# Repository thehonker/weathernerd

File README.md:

# WeatherNerd

Low-power, long-duration weather stations built around the [WindNerd Core](https://github.com/windnerd-labs/Windnerd-Core) anemometer and ESP32-C6 dataloggers.

## What is this?

Two station variants sharing the same wind sensor and datalogger platform:

### Remote Station (v1)

A battery-powered, 6-month-unattended weather station for remote deployment. No grid power, no WiFi infrastructure, no maintenance visits. Deploy in fall, retrieve in spring.

- **Wind:** WindNerd Core (STM32G031F8) with custom firmware — STOP mode sleep (~5 µA), woken on demand by ESP32-C6 every 5s via GPIO interrupt. Wind speed via rotor pulse counting, direction via TMAG5273 magnetic angle sensor.
- **Datalogger:** ESP32-C6 SuperMini, running **ESP-IDF v6.1** (not Arduino — the LP RISC-V coprocessor requires ESP-IDF's `ulp_embed_binary` build system). LP core handles the 5s wind sampling loop while the main core sleeps (~7 µA deep sleep). Main core wakes every 1 min for temp/RH/pressure, rain ADC, and SD card flush.
- **Sensors:** BME280 (temp/RH/pressure, I2C), DS3231 RTC (±2 ppm, I2C), DIY piezo disdrometer (ADC, rain rate).
- **Storage:** 8 GB industrial microSD via SPI. Two daily CSV files: `YYYY-MM-DD-wind.csv` (5s samples) and `YYYY-MM-DD-env.csv` (1 min samples). ~168 MB for 6 months.
- **Power:** 2× ER34615 Li-SOCl2 D-cells (38 Ah, -55°C rated). Total system draw ~0.55 mA (16× battery headroom over 6 months). Battery lasts years — power is a non-issue.
- **Uplink:** SIM7080G Cat-M1 modem on AT&T LTE-M network. MQTT uplink every 30 min with buffered data. Daily GPS fix via SIM7080G GNSS syncs the DS3231 RTC, eliminating long-term drift. PSM sleep (~3 µA module) between uploads.
- **Retrieval:** Press CON button on the enclosure → ESP32-C6 powers on OLED display + starts WiFi 6 soft-AP. Connect with phone/laptop, browse and download CSV files. Rotary encoder + OLED for on-device UI. LTE-M uplink provides live data during deployment — WiFi is for full bulk download on physical retrieval.
- **Antenna:** Directional Yagi (700–2700 MHz) aimed at nearest AT&T tower for LTE-M. Passive GNSS patch antenna (25×25mm) for daily GPS RTC sync.
- **Cost:** ~$214-283 total BOM.

### Home Station (future)

A wall-powered variant for permanent installation at home. Same WindNerd Core + ESP32-C6 platform, but always-on WiFi with Prometheus-style metrics exposure:

- `/metrics` endpoint scraped by a Prometheus instance
- Wind speed, direction, temperature, RH, pressure, rain rate as gauge metrics
- DS3231 RTC for timestamp accuracy
- No battery, no SD card — data lives in Prometheus
- OLED + encoder UI always available
- Optional: push to a remote station's data archive for cross-site comparison

Design docs for the home station will be added when we start that phase. The remote station firmware and hardware are the priority — the home station reuses the same components and most of the same firmware.

## Repo layout

```none
weathernerd/
├── README.md              ← you are here
├── LICENSE
├── .github/workflows/
│   └── build-windnerd-stm32g031f8.yml  ← CI/CD for STM32 firmware
└── local-storage/
    ├── notes/
    │   ├── hardware-design.md   ← pin allocation, wiring, BOM, component selection
    │   ├── power-budget.md      ← current draw analysis, battery sizing
    │   ├── storage-budget.md    ← data volume, SD card selection, file strategy
    │   └── lte-uplink.md        ← LTE-M modem options, antenna, SIM, power impact
    └── firmware/
        ├── windnerd-stm32g031f8/  ← custom WindNerd Core firmware (⚠️ WIP, untested)
        │   ├── README.md           ← firmware docs, build & flash instructions
        │   ├── build.sh            ← build locally (Docker)
        │   ├── flash.sh            ← flash via ST-Link (Docker)
        │   ├── src/src.ino         ← firmware source
        │   ├── lib/Windnerd-Core/  ← git submodule
        │   └── build-env/          ← Dockerfile + compile/flash scripts
        └── esp32c6-supermini/     ← ESP32-C6 datalogger firmware (ESP-IDF, ✅ compiles)
            ├── README.md           ← firmware docs, build & flash instructions
            ├── CMakeLists.txt      ← ESP-IDF project root
            ├── sdkconfig.defaults  ← LP core, FAT/SD, WiFi AP, BT disabled
            ├── partitions.csv      ← nvs + phy + 3 MB factory
            ├── build.sh            ← build locally (Docker)
            ├── flash.sh            ← flash via USB serial (Docker)
            ├── main/
            │   ├── CMakeLists.txt  ← ulp_embed_binary() for LP core
            │   ├── main.c          ← main core firmware
            │   ├── storage.h/.c    ← SDSPI + CSV writing (wind + env)
            │   ├── i2c_bus.h/.c    ← shared I2C bus (GPIO6/7)
            │   ├── ds3231.h/.c     ← DS3231 RTC driver
            │   ├── bme280.h/.c     ← BME280 driver + compensation
            │   ├── wifi.h/.c         ← WiFi AP + HTTP server (files, clock, format, reboot, halt)
            │   ├── oled.h/.c       ← SH1106 OLED driver (128×64, text)
            │   ├── oled_font.h     ← 8×8 ASCII font
            │   ├── input.h/.c      ← EC11 encoder + CON/BAK/PSH buttons
            │   ├── ui.h/.c         ← Interactive menu UI (6 items)
            │   └── lp_core/main.c  ← LP core firmware
            └── build-env/          ← Dockerfile (espressif/idf:release-v6.1)
```

## Design docs

Start with [hardware-design.md](local-storage/notes/hardware-design.md) for the full system overview, pin allocation, and BOM.
[power-budget.md](local-storage/notes/power-budget.md) covers current draw and battery life.
[storage-budget.md](local-storage/notes/storage-budget.md) covers data volumes and SD card selection.
[lte-uplink.md](local-storage/notes/lte-uplink.md) covers LTE-M modem selection, antenna, SIM, and power budget impact.

## Firmware

### WindNerd Core (STM32G031F8) — ⚠️ WIP, untested - compiles, sensors implemented

Custom firmware replacing the factory WindNerd Core firmware. Drops power from ~0.6 mA (SLEEP mode) to ~0.04 mA (STOP mode) by sleeping until the ESP32-C6 triggers a read via GPIO interrupt. Uses the TMAG5273 driver directly from the WindNerd Core library — the `WN_Core` class is not used.

- **Status:** Written, compiles clean (62% flash, 25% RAM), not yet tested on hardware
- **Build:** `./build.sh` (Docker, no host tooling needed) → `build/src.ino.bin`
- **Flash:** `./flash.sh` (ST-Link V2, openocd in Docker) or `./flash.sh --ci` (download from GitHub releases)
- **CI/CD:** Auto-builds on push to main, publishes env image to GHCR + GitHub release with firmware binaries
- **Details:** [windnerd-stm32g031f8/README.md](local-storage/firmware/windnerd-stm32g031f8/README.md)

### ESP32-C6 SuperMini — ⚠️ WIP, untested — compiles, all features implemented

ESP32-C6 datalogger firmware built with **ESP-IDF v6.1**. The LP RISC-V coprocessor handles the 5s wind sampling loop (WindNerd trigger + UART RX) while the main core sleeps. Main core wakes every 1 min for sensors + SD card flush. Interactive UI (OLED + encoder + buttons) triggered by CON button press — provides live data, file browser, WiFi portal, clock sync, format SD, reboot, sleep, and halt.

- **Status:** All firmware modules written and compiling clean. Full data flow implemented: LP core samples wind every 5s → main core flushes to SD every 1 min. Interactive UI with 8 menu items. WiFi portal with file browser, clock sync, format SD, reboot, halt. Only hardware testing remains.
- **Binary:** 1.15 MB (37% of 3 MB factory partition — WiFi stack adds ~800 KB)
- **Build:** `./build.sh` (Docker, no host toolchain needed) → `build/esp32c6_weathernerd.bin`
- **Flash:** `./flash.sh` (USB serial, esptool in Docker) or `./flash.sh --ci` (download from GitHub releases)
- **CI/CD:** Auto-builds on push, publishes env image to GHCR + GitHub release with firmware binaries
- **Details:** [esp32c6-supermini/README.md](local-storage/firmware/esp32c6-supermini/README.md)

**Why ESP-IDF, not Arduino?** The ESP32-C6's LP RISC-V coprocessor is the whole reason we chose the C6 over the C3. Arduino-esp32 does not support LP core programming — no `ulp_embed_binary()` build pipeline, no LP core API exposure. ESP-IDF is the official framework for LP core development.

## Key design decisions

- **WindNerd custom firmware** — factory firmware draws 0.6 mA. Custom STOP mode + on-demand sampling drops it to ~0.04 mA. 7× total system power reduction.
- **ESP32-C6 over ESP32-C3** — the C6's LP RISC-V coprocessor handles the 5s sampling loop while the main core sleeps. The C3 has no LP core, so the main core would wake every 5s, roughly doubling power consumption. This required switching from Arduino to ESP-IDF — Arduino-esp32 doesn't support LP core programming.
- **No solar** — at 0.55 mA average, the battery alone has 16× headroom over 6 months. Solar adds complexity and failure modes for zero benefit.
- **Two data streams** — wind+rain at 5s (LP core) and temp/RH/pressure at 1 min (main core). Separate daily CSV files. Temp changes slowly; 1 min is plenty.
- **CON button + OLED** — the station sleeps with zero UI. A momentary button (CON) wakes the main core via GPIO interrupt, firmware powers on the OLED via MOSFET (GPIO5), and starts a WiFi AP for data retrieval. Zero power when off. BAK button at top-level menu returns to low-power mode. 60s inactivity timeout as backup. A future "Halt" option (full system stop, power cycle to resume) may be added to both the OLED menu and WiFi portal.
- **SPI over SDIO for SD card** — GPIO18–23 are the ESP32-C6's native SDIO peripheral, but 4-bit SDIO needs 6 pins and would eat GPIO20/21 (encoder) and GPIO22/23 (CON/BAK buttons). SPI mode uses 4 pins and the data rate is trivial (~838 KB/day, 70-byte appends once per minute). The SD card is asleep 55s out of every 60s — SDIO's speed advantage is irrelevant. The saved pins keep the encoder and buttons on safe, non-strapping GPIO.
- **DIY piezo disdrometer** — no moving parts, $2 in parts, logs raw ADC peaks. Calibrate later against a reference gauge. v1 has no op-amp (simplest); v2 adds OPA376 if drizzle sensitivity is needed.
- **SIM7080G LTE-M uplink** — Cat-M1 on AT&T (the only carrier with coverage at the deployment site). PSM sleep at ~3 µA between 30-min MQTT uploads. LC filter on VBAT handles Cat-M1 TX spikes from the high-internal-resistance Li-SOCl2 battery. Daily GPS fix via the modem's GNSS receiver syncs the DS3231 RTC, eliminating ±5 min drift over 6 months. NB-IoT is dead on AT&T (sunset Q1 2025) — Cat-M1 is the only viable low-power IoT option.

## License

`AGPL-3.0-or-later`. See [LICENSE](LICENSE).

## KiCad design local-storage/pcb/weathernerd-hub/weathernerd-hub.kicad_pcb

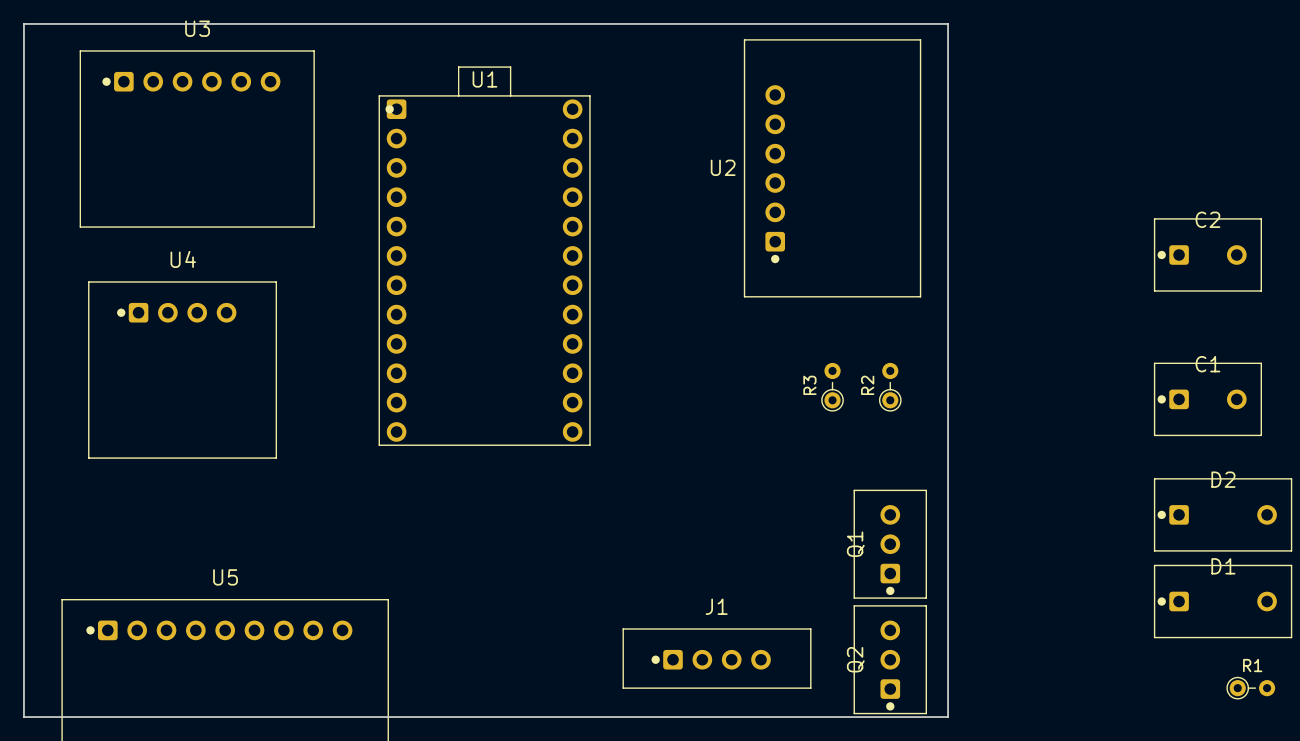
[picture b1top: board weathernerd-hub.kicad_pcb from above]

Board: 2 copper layers, 80.0 x 60.0 mm, 15 parts (0 on the bottom side), 18 nets, no tracks yet.

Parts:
C1: 1nF; C1
C2: 470nF; C2
D1: 1N4148; D1
D2: 1N4148; D2
J1: WindNerd-Conn
Q1: 2N7002; Q1
Q2: AO3401; Q2
R1, R2, R3: 10k; R_Axial_DIN0204_L3.6mm_D1.6mm_P2.54mm_Vertical
U1: ESP32-C6-SuperMini
U2: MicroSD-SPI
U3: BME280
U4: DS3231
U5: OLED-Encoder-Btns

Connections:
+3V3: J1.VCC, Q2.S, R3.2, U1.3V3, U2.3V3, U3.VCC, U4.VCC
BAK_BTN: U1.23 (IO23), U5.BAK
CON_BTN: U1.22 (IO22), U5.CON
ENC_A: U1.14 (IO14), U5.TRA
ENC_B: U1.20 (IO20), U5.TRB
GND: C2.2, J1.GND, Q1.S, R2.2, U1.GND, U2.GND, U3.GND, U4.GND, U5.GND
I2C_SCL: U1.7 (IO7), U3.SCL, U4.SCL, U5.SCL
I2C_SDA: U1.6 (IO6), U3.SDA, U4.SDA, U5.SDA
OLED_GATE: Q2.G, R3.1, U1.5 (IO5)
OLED_PWR: Q2.D, U5.VCC
PEAK: C2.1, Q1.D, R1.1
RAIN_ADC: R1.2, U1.0 (IO0)
RAIN_RST: Q1.G, R2.1, U1.8 (IO8)
SPI_CS: U1.3 (IO3), U2.CS
SPI_MISO: U1.19 (IO19), U2.MISO
SPI_MOSI: U1.18 (IO18), U2.MOSI
WIND_TRIG: J1.TRG, U1.1 (IO1)
WIND_TX: J1.RX, U1.4 (IO4)
